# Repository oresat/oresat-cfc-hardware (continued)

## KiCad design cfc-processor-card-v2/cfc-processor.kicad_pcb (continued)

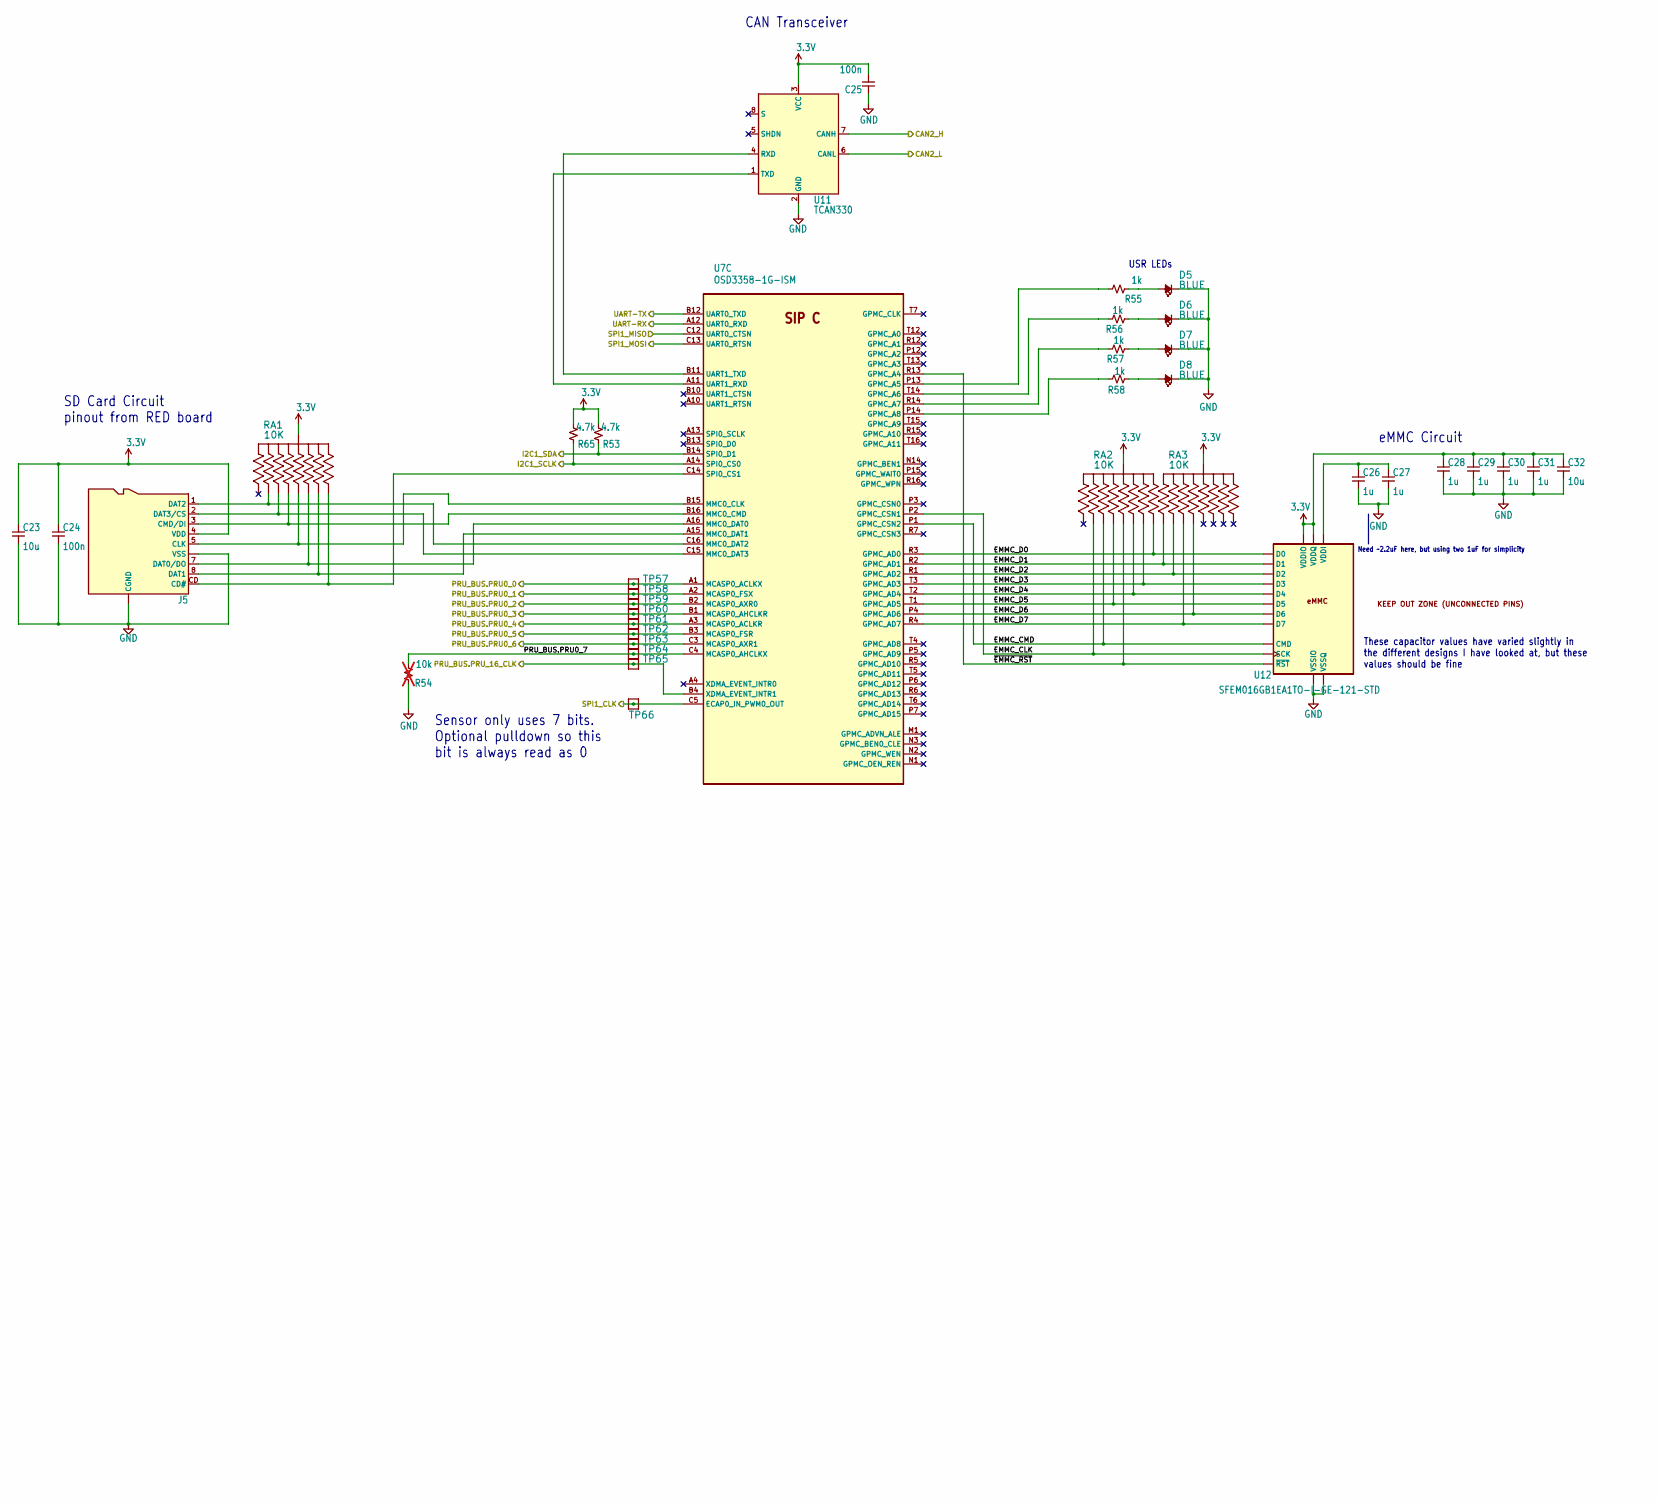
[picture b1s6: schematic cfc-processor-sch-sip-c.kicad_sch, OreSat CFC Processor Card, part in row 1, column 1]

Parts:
C23, C32: 10u; 0805-C-NOSILK; MPN GRT21BC71E106KE13K
C24, C25: 100n; 0603-C-NOSILK; MPN C0603C104K5RACAUTO
C26, C27, C28, C29, C30, C31: 1u; 0603-C-NOSILK; MPN GCM21BR71H105KA03L
D5, D6, D7, D8: BLUE; LED_0603_1608Metric; MPN 150060BS75000
J5: DM3BT-DSF-PEJS; J-Hirose-DM3BT-DSF-PEJS; MPN DM3BT-DSF-PEJS
R53, R65: 4.7k; 0603-C-NOSILK; MPN RMCF0603FT4K70
R54: 10k; 0603-C-NOSILK; not fitted
R55, R56, R57, R58: 1k; 0603-C-NOSILK; MPN RMCF0603FT1K00
RA1, RA2, RA3: 10K; ARRAY_EXBA-M; MPN EXB-A10P103J
TP57, TP58, TP59, TP60, TP61, TP62, TP63, TP64, TP65, TP66: TEST-POINT; 2MM-TEST-POINT
U7: OSD3358-1G-ISM; U-Octavo-OSD335X-BGA-256; MPN OSD3358-1G-ISM
U11: TCAN330; SOT-23-8; MPN TCAN330GDCNT
U12: SFEM016GB1EA1TO-I-GE-121-STD; BGA-153(11.5X13)(EMMC-BA); MPN SFEM016GB1EA1TO-I-GE-121-STD

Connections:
3.3V: C23.1, C24.1, C25.2, C28.1, C29.1, C30.1, C31.1, C32.1, J5.4 (VDD), R53.2, R65.2, RA1.5 (55), RA1.10 (55), RA2.5 (55), RA2.10 (55), RA3.5 (55), RA3.10 (55), U11.3 (VCC), U12.C6 (VDDQ), U12.E6 (VDDIO), U12.F5 (VDDIO), U12.J10 (VDDIO), U12.K9 (VDDIO), U12.M4 (VDDQ), U12.N4 (VDDQ), U12.P3 (VDDQ), U12.P5 (VDDQ); also elsewhere on the board
/CAN2_H: U11.7 (CANH); also elsewhere on the board
/CAN2_L: U11.6 (CANL); also elsewhere on the board
/Deserializer/PRU_BUS.PRU0_0: TP57.1 (1_1), U7.A1 (MCASP0_ACLKX); also elsewhere on the board
/Deserializer/PRU_BUS.PRU0_1: TP58.1 (1_1), U7.A2 (MCASP0_FSX); also elsewhere on the board
/Deserializer/PRU_BUS.PRU0_2: TP59.1 (1_1), U7.B2 (MCASP0_AXR0); also elsewhere on the board
/Deserializer/PRU_BUS.PRU0_3: TP60.1 (1_1), U7.B1 (MCASP0_AHCLKR); also elsewhere on the board
/Deserializer/PRU_BUS.PRU0_4: TP61.1 (1_1), U7.A3 (MCASP0_ACLKR); also elsewhere on the board
/Deserializer/PRU_BUS.PRU0_5: TP62.1 (1_1), U7.B3 (MCASP0_FSR); also elsewhere on the board
/Deserializer/PRU_BUS.PRU0_6: TP63.1 (1_1), U7.C3 (MCASP0_AXR1); also elsewhere on the board
/Deserializer/PRU_BUS.PRU_16_CLK: TP65.1 (1_1), U7.B4 (XDMA_EVENT_INTR1); also elsewhere on the board
/I2C1_CLK: R65.1, U7.A14 (SPI0_CS0); also elsewhere on the board
/I2C1_SDA: R53.1, U7.B14 (SPI0_D1); also elsewhere on the board
/OSD3358: SIP C/EMMC_CLK: RA2.9 (99), U7.P2 (GPMC_CSN1), U12.M6 (SCK)
/OSD3358: SIP C/EMMC_CMD: RA2.2 (22), U7.P1 (GPMC_CSN2), U12.M5 (CMD)
/OSD3358: SIP C/EMMC_D0: RA2.6 (66), U7.R3 (GPMC_AD0), U12.A3 (D0)
/OSD3358: SIP C/EMMC_D1: RA3.1 (11), U7.R2 (GPMC_AD1), U12.A4 (D1)
/OSD3358: SIP C/EMMC_D2: RA3.9 (99), U7.R1 (GPMC_AD2), U12.A5 (D2)
/OSD3358: SIP C/EMMC_D3: RA2.4 (44), U7.T3 (GPMC_AD3), U12.B2 (D3)
/OSD3358: SIP C/EMMC_D4: RA2.7 (77), U7.T2 (GPMC_AD4), U12.B3 (D4)
/OSD3358: SIP C/EMMC_D5: RA2.8 (88), U7.T1 (GPMC_AD5), U12.B4 (D5)
/OSD3358: SIP C/EMMC_D6: RA3.8 (88), U7.P4 (GPMC_AD6), U12.B5 (D6)
/OSD3358: SIP C/EMMC_D7: RA3.2 (22), U7.R4 (GPMC_AD7), U12.B6 (D7)
/OSD3358: SIP C/PRU_BUS.PRU0_7: R54.2, TP64.1 (1_1), U7.C4 (MCASP0_AHCLKX)
/OSD3358: SIP C/UART-RX: U7.A12 (UART0_RXD); also elsewhere on the board
/OSD3358: SIP C/UART-TX: U7.B12 (UART0_TXD); also elsewhere on the board
/OSD3358: SIP C/~EMMC_RST: RA2.3 (33), U7.R13 (GPMC_A4), U12.K5 (~RST)
/SPI1_CLK: TP66.1 (1_1), U7.C5 (ECAP0_IN_PWM0_OUT); also elsewhere on the board
/SPI1_MISO: U7.C12 (UART0_CTSN); also elsewhere on the board
/SPI1_MOSI: U7.C13 (UART0_RTSN); also elsewhere on the board
GND: C23.2, C24.2, C25.1, C26.2, C27.2, C28.2, C29.2, C30.2, C31.2, C32.2, D5.1 (K), D6.1 (K), D7.1 (K), D8.1 (K), J5.6 (VSS), J5.CGND1 (CGND), J5.CGND2 (CGND), J5.CGND3 (CGND), J5.CGND4 (CGND), J5.CGND5 (CGND), J5.CGND6 (CGND), J5.GND (VSS), R54.1, U11.2 (GND), U12.A6 (VSSIO), U12.C4 (VSSQ), U12.E7 (VSSIO), U12.G5 (VSSIO), U12.H10 (VSSIO), U12.J5 (VSSIO), U12.K8 (VSSIO), U12.N2 (VSSQ), U12.N5 (VSSQ), U12.P4 (VSSQ), U12.P6 (VSSQ); also elsewhere on the board
unnamed: D5.2 (A), R55.2
unnamed: D6.2 (A), R56.2
unnamed: D7.2 (A), R57.2
unnamed: D8.2 (A), R58.2
unnamed: J5.CD (CD#), RA1.6 (66), U7.C14 (SPI0_CS1)
unnamed: J5.5 (CLK), RA1.3 (33), U7.B15 (MMC0_CLK)
unnamed: J5.3 (CMD/DI), RA1.8 (88), U7.B16 (MMC0_CMD)
unnamed: J5.7 (DAT0/DO), RA1.7 (77), U7.A16 (MMC0_DAT0)
unnamed: J5.8 (DAT1), RA1.4 (44), U7.A15 (MMC0_DAT1)
unnamed: J5.1 (DAT2), RA1.9 (99), U7.C16 (MMC0_DAT2)
unnamed: J5.2 (DAT3/CS), RA1.2 (22), U7.C15 (MMC0_DAT3)
unnamed: R55.1, U7.P13 (GPMC_A5)
unnamed: R56.1, U7.T14 (GPMC_A6)
unnamed: R57.1, U7.R14 (GPMC_A7)
unnamed: R58.1, U7.P14 (GPMC_A8)
unnamed: U7.B11 (UART1_TXD), U11.4 (RXD)
unnamed: U7.A11 (UART1_RXD), U11.1 (TXD)
unnamed: C26.1, C27.1, U12.C2 (VDDI)

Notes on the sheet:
USR LEDs
Sensor only uses 7 bits. Optional pulldown so this bit is always read as 0
Need ~2.2uF here, but using two 1uF for simplicity
SD Card Circuit pinout from RED board
1.2
These capacitor values have varied slightly in the different designs I have looked at, but these values should be fine
CAN Transceiver
eMMC Circuit

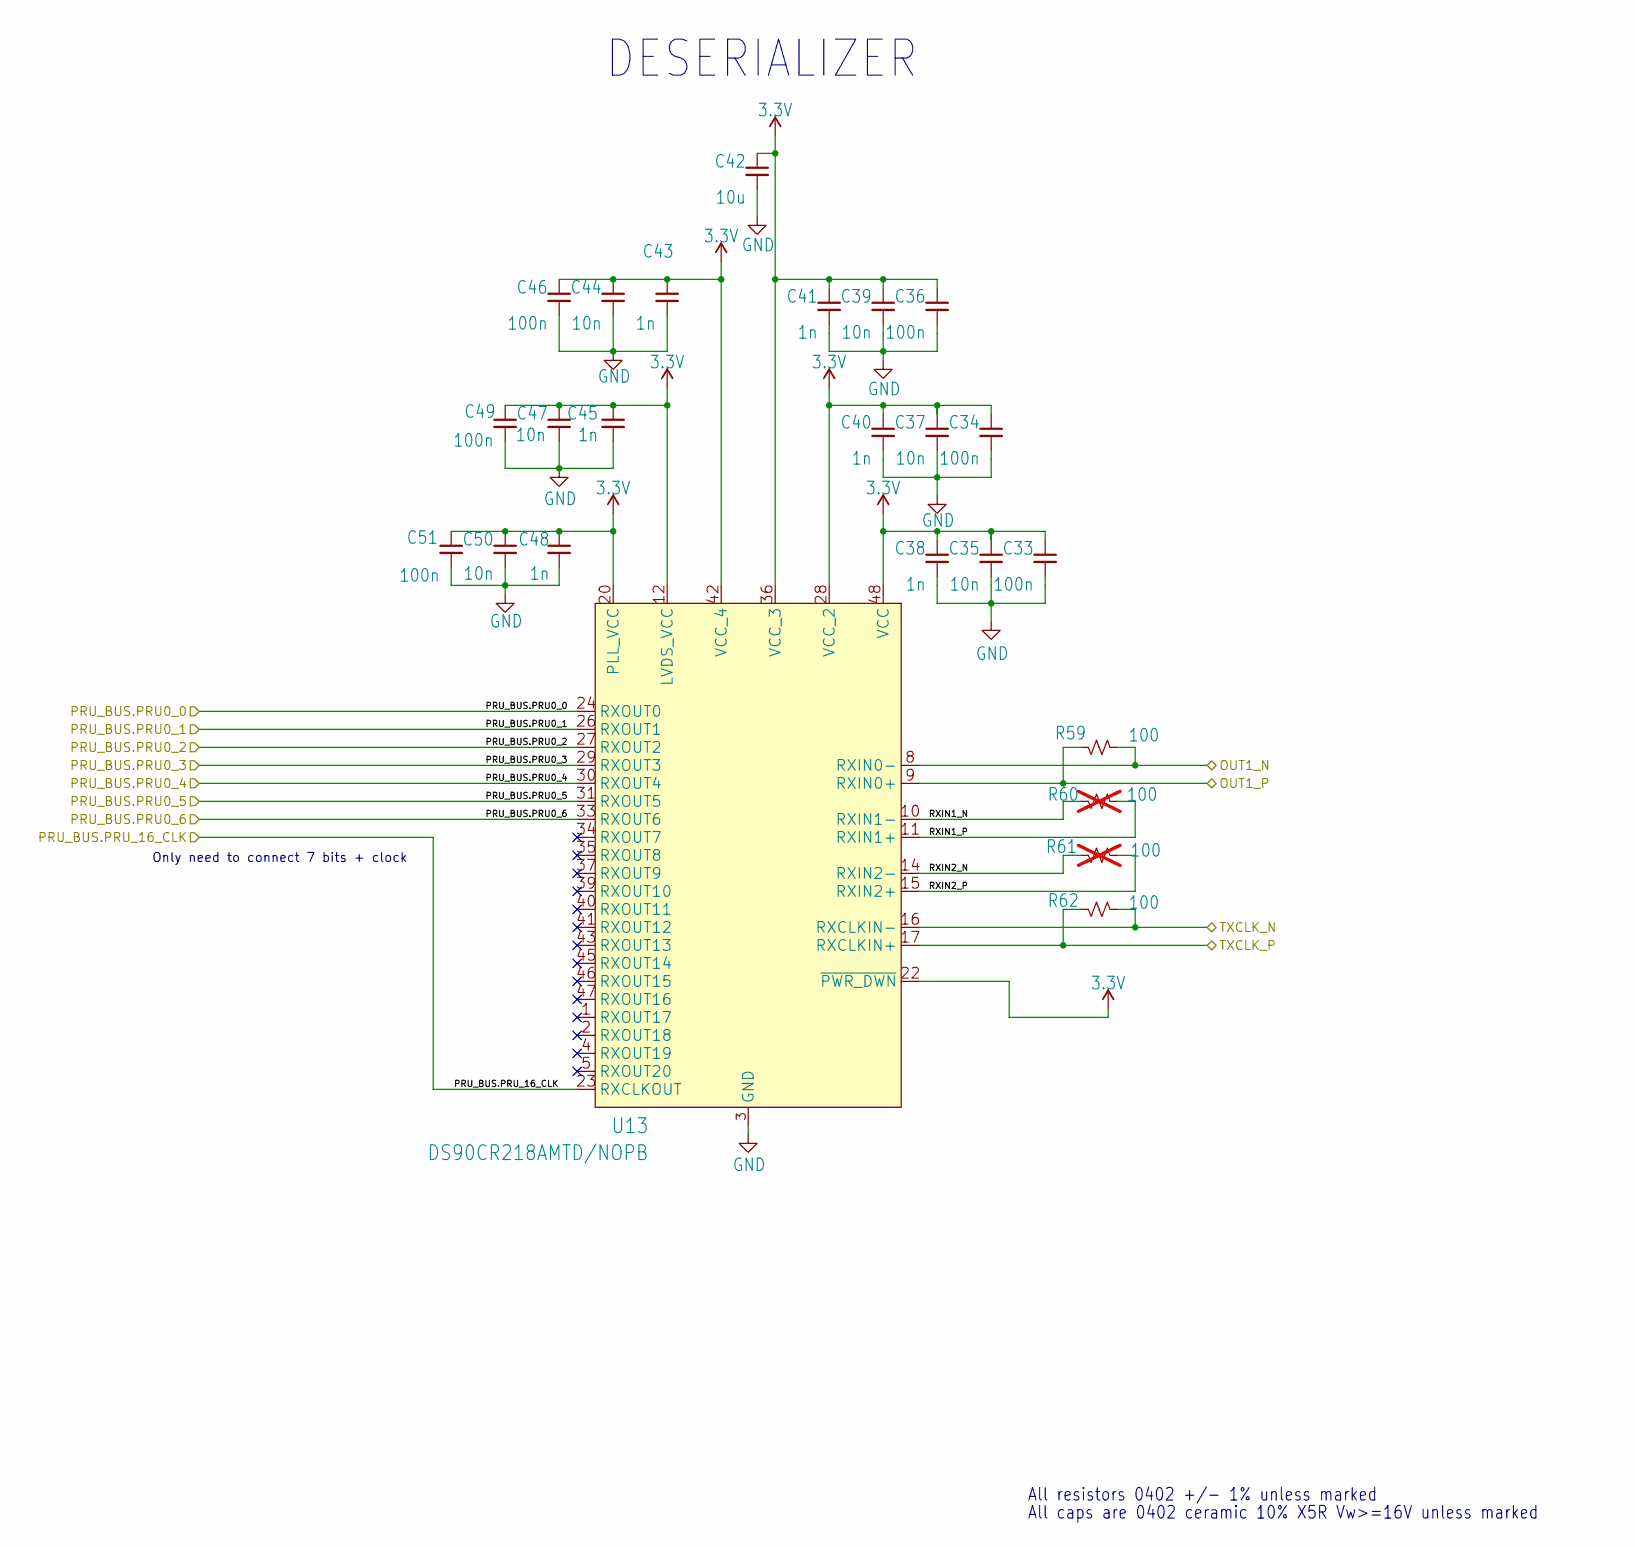
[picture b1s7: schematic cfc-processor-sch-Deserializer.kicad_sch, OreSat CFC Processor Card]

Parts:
C33, C34, C36, C46, C49, C51: 100n; 0402-C-NOSILK; MPN C0402C104K4RECAUTO
C35, C37, C39, C44, C47, C50: 10n; 0402-C-NOSILK; MPN GXT155R71E103KE01D
C38, C40, C41, C43, C45, C48: 1n; 0402-C-NOSILK; MPN C0402C102J3GACAUTO
C42: 10u; 0805-C-NOSILK; MPN GRT21BC71E106KE13K
R59, R62: 100; 0402-C-NOSILK; MPN RMCF0402FT100R
R60, R61: 100; 0402-C-NOSILK; MPN RC0201FR-07100RL; not fitted
U13: DS90CR218AMTD/NOPB; MTD48_TEX-L; MPN DS90CR218AMTD/NOPB

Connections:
3.3V: C33.1, C34.1, C35.1, C36.1, C37.1, C38.1, C39.1, C40.1, C41.1, C42.1, C43.1, C44.1, C45.1, C46.1, C47.1, C48.1, C49.1, C50.1, C51.1, U13.12 (LVDS_VCC), U13.20 (PLL_VCC), U13.22 (~PWR_DWN), U13.28 (VCC_2), U13.36 (VCC_3), U13.42 (VCC_4), U13.48 (VCC); also elsewhere on the board
/Deserializer/PRU_BUS.PRU0_0: U13.24 (RXOUT0); also elsewhere on the board
/Deserializer/PRU_BUS.PRU0_1: U13.26 (RXOUT1); also elsewhere on the board
/Deserializer/PRU_BUS.PRU0_2: U13.27 (RXOUT2); also elsewhere on the board
/Deserializer/PRU_BUS.PRU0_3: U13.29 (RXOUT3); also elsewhere on the board
/Deserializer/PRU_BUS.PRU0_4: U13.30 (RXOUT4); also elsewhere on the board
/Deserializer/PRU_BUS.PRU0_5: U13.31 (RXOUT5); also elsewhere on the board
/Deserializer/PRU_BUS.PRU0_6: U13.33 (RXOUT6); also elsewhere on the board
/Deserializer/PRU_BUS.PRU_16_CLK: U13.23 (RXCLKOUT); also elsewhere on the board
/Deserializer/RXIN1_N: R60.2, U13.10 (RXIN1-)
/Deserializer/RXIN1_P: R60.1, U13.11 (RXIN1+)
/Deserializer/RXIN2_N: R61.2, U13.14 (RXIN2-)
/Deserializer/RXIN2_P: R61.1, U13.15 (RXIN2+)
/OUT1_N: R59.2, U13.8 (RXIN0-); also elsewhere on the board
/OUT1_P: R59.1, U13.9 (RXIN0+); also elsewhere on the board
/TXCLK_N: R62.1, U13.16 (RXCLKIN-); also elsewhere on the board
/TXCLK_P: R62.2, U13.17 (RXCLKIN+); also elsewhere on the board
GND: C33.2, C34.2, C35.2, C36.2, C37.2, C38.2, C39.2, C40.2, C41.2, C42.2, C43.2, C44.2, C45.2, C46.2, C47.2, C48.2, C49.2, C50.2, C51.2, U13.3 (GND), U13.7 (GND), U13.13 (GND), U13.18 (GND), U13.19 (GND), U13.21 (GND), U13.25 (GND), U13.32 (GND), U13.38 (GND), U13.44 (GND); also elsewhere on the board

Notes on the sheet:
All caps are 0402 ceramic 10% X5R Vw>=16V unless marked
All resistors 0402 +/- 1% unless marked
Only need to connect 7 bits + clock
DESERIALIZER

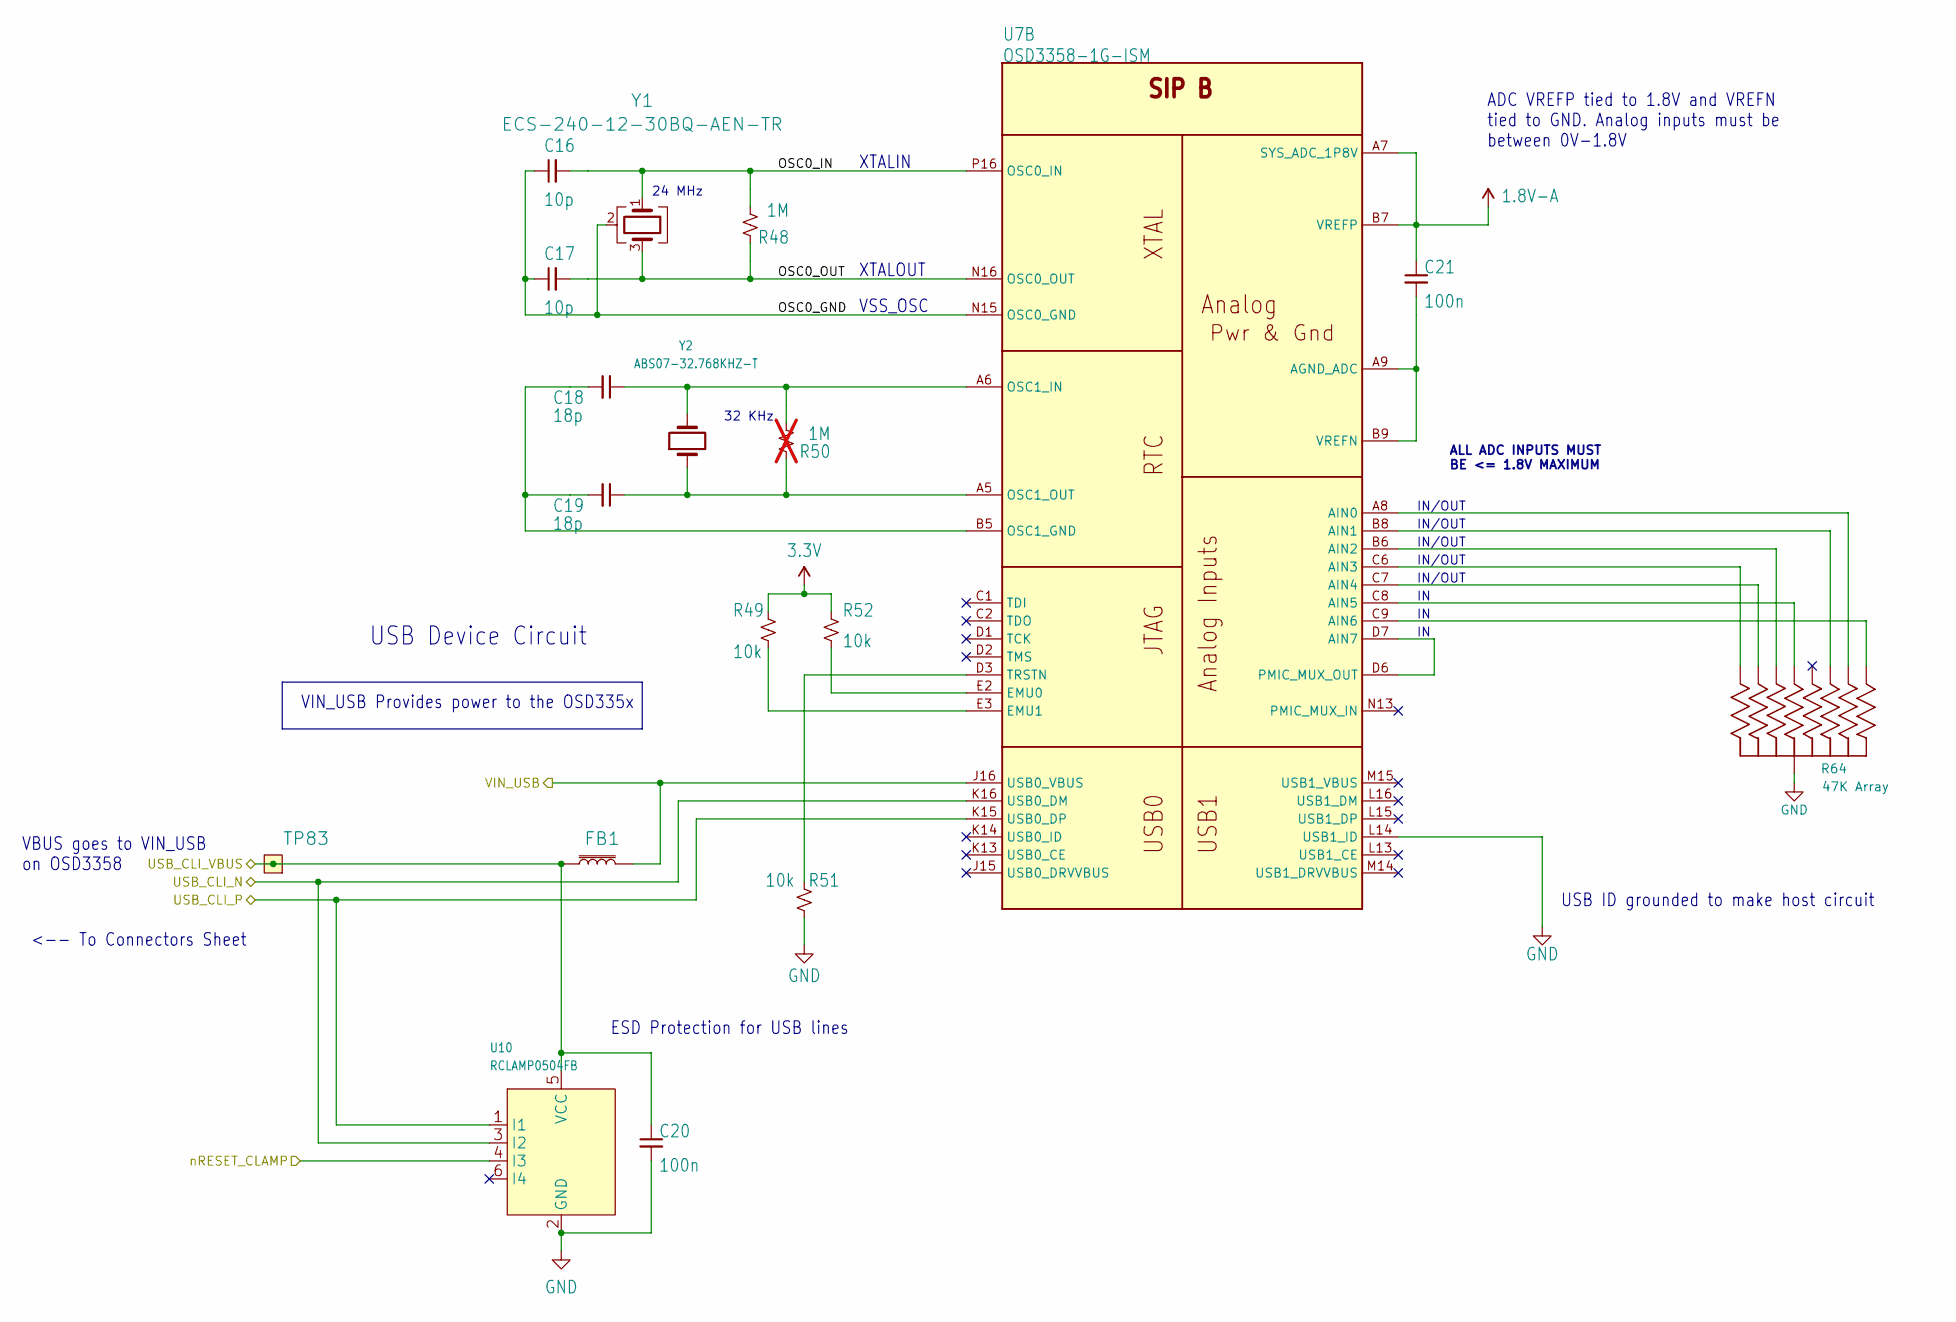
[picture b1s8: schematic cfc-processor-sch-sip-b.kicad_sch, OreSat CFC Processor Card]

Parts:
C16, C17: 10p; 0603-C-NOSILK; MPN C0603C100J1GACAUTO
C18, C19: 18p; 0603-C-NOSILK; MPN C0603C180J1GACAUTO
C20, C21: 100n; 0603-C-NOSILK; MPN C0603C104K5RACAUTO
FB1: BLM18KG300JH1D; L_0603_1608Metric; MPN BLM18KG300JH1D
R48: 1M; 0603-C-NOSILK; MPN RMCF0603FG1M00
R49, R51, R52: 10k; 0603-C-NOSILK; MPN RMCF0603FT10K0
R50: 1M; 0603-C-NOSILK; not fitted
R64: 47K Array; ARRAY_EXBA-M; MPN EXB-A10P473J
TP83: TEST-POINT; TestPoint-0.75mm-th
U7: OSD3358-1G-ISM; U-Octavo-OSD335X-BGA-256; MPN OSD3358-1G-ISM
U10: RCLAMP0504FB; SC70-6; MPN RCLAMP0504FBTCT
Y1: ECS-240-12-30BQ-AEN-TR; CRYSTAL-5X3.2-4SMD; MPN ECS-240-12-30BQ-AEN-TR
Y2: ABS07-32.768KHZ-T; CRYSTAL_3.2X1.5; MPN ABS07-32.768KHZ-T

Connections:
1.8V-A: C21.1, U7.A7 (SYS_ADC_1P8V), U7.B7 (VREFP)
3.3V: R49.2, R52.2; also elsewhere on the board
/OSD3358: SIP A (PWR)/NRESET: U10.4 (I3); also elsewhere on the board
/OSD3358: SIP A (PWR)/VIN_USB: FB1.2, U7.J16 (USB0_VBUS); also elsewhere on the board
/OSD3358: SIP B/OSC0_GND: C16.1, C17.1, U7.N15 (OSC0_GND), Y1.2 (G), Y1.4 (G)
/OSD3358: SIP B/OSC0_IN: C16.2, R48.2, U7.P16 (OSC0_IN), Y1.1
/OSD3358: SIP B/OSC0_OUT: C17.2, R48.1, U7.N16 (OSC0_OUT), Y1.3
/OSD3358: SIP B/USB_CLI_N: U7.K16 (USB0_DM), U10.3 (I2); also elsewhere on the board
/OSD3358: SIP B/USB_CLI_P: U7.K15 (USB0_DP), U10.1 (I1); also elsewhere on the board
/OSD3358: SIP B/USB_CLI_VBUS: C20.1, FB1.1, TP83.1 (1_1), U10.5 (VCC); also elsewhere on the board
GND: C20.2, R51.1, R64.5 (55), R64.10 (55), U7.L14 (USB1_ID), U10.2 (GND); also elsewhere on the board
unnamed: R64.1 (11), U7.C9 (AIN6)
unnamed: R64.2 (22), U7.B8 (AIN1)
unnamed: R64.3 (33), U7.C8 (AIN5)
unnamed: R64.4 (44), U7.C7 (AIN4)
unnamed: R64.6 (66), U7.C6 (AIN3)
unnamed: R64.7 (77), U7.B6 (AIN2)
unnamed: R64.9 (99), U7.A8 (AIN0)
unnamed: C21.2, U7.A9 (AGND_ADC), U7.B9 (VREFN)
unnamed: U7.D6 (PMIC_MUX_OUT), U7.D7 (AIN7)
unnamed: R52.1, U7.E2 (EMU0)
unnamed: R49.1, U7.E3 (EMU1)
unnamed: C18.2, C19.2, U7.B5 (OSC1_GND)
unnamed: C18.1, R50.2, U7.A6 (OSC1_IN), Y2.2
unnamed: C19.1, R50.1, U7.A5 (OSC1_OUT), Y2.1
unnamed: R51.2, U7.D3 (TRSTN)

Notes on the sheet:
XTALOUT
IN/OUT
<-- To Connectors Sheet
USB ID grounded to make host circuit
VSS_OSC
ADC VREFP tied to 1.8V and VREFN tied to GND. Analog inputs must be between 0V-1.8V
VBUS goes to VIN_USB on OSD3358
USB Device Circuit
VIN_USB Provides power to the OSD335x
ESD Protection for USB lines
24 MHz
ALL ADC INPUTS MUST BE <= 1.8V MAXIMUM
32 KHz
XTALIN

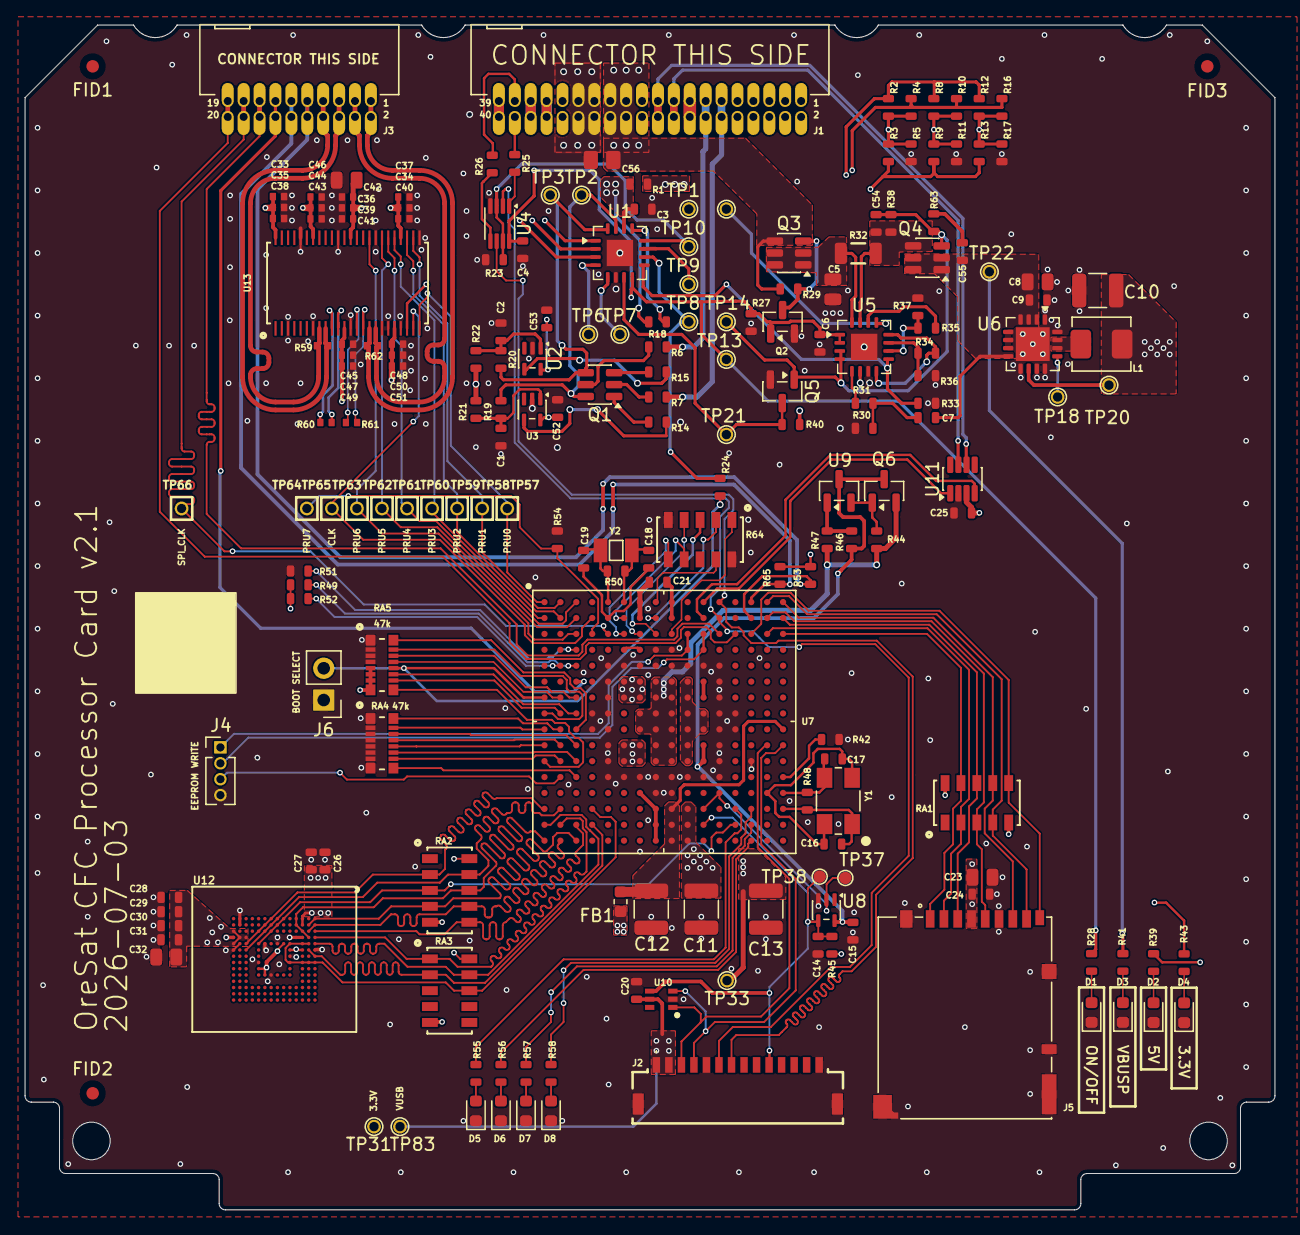
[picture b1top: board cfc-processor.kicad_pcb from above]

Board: 4 copper layers, 99.8 x 94.6 mm, 196 parts (0 on the bottom side), 165 nets.

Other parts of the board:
PCB1: ORESAT-CARD-V1.3-GENERIC-0RF

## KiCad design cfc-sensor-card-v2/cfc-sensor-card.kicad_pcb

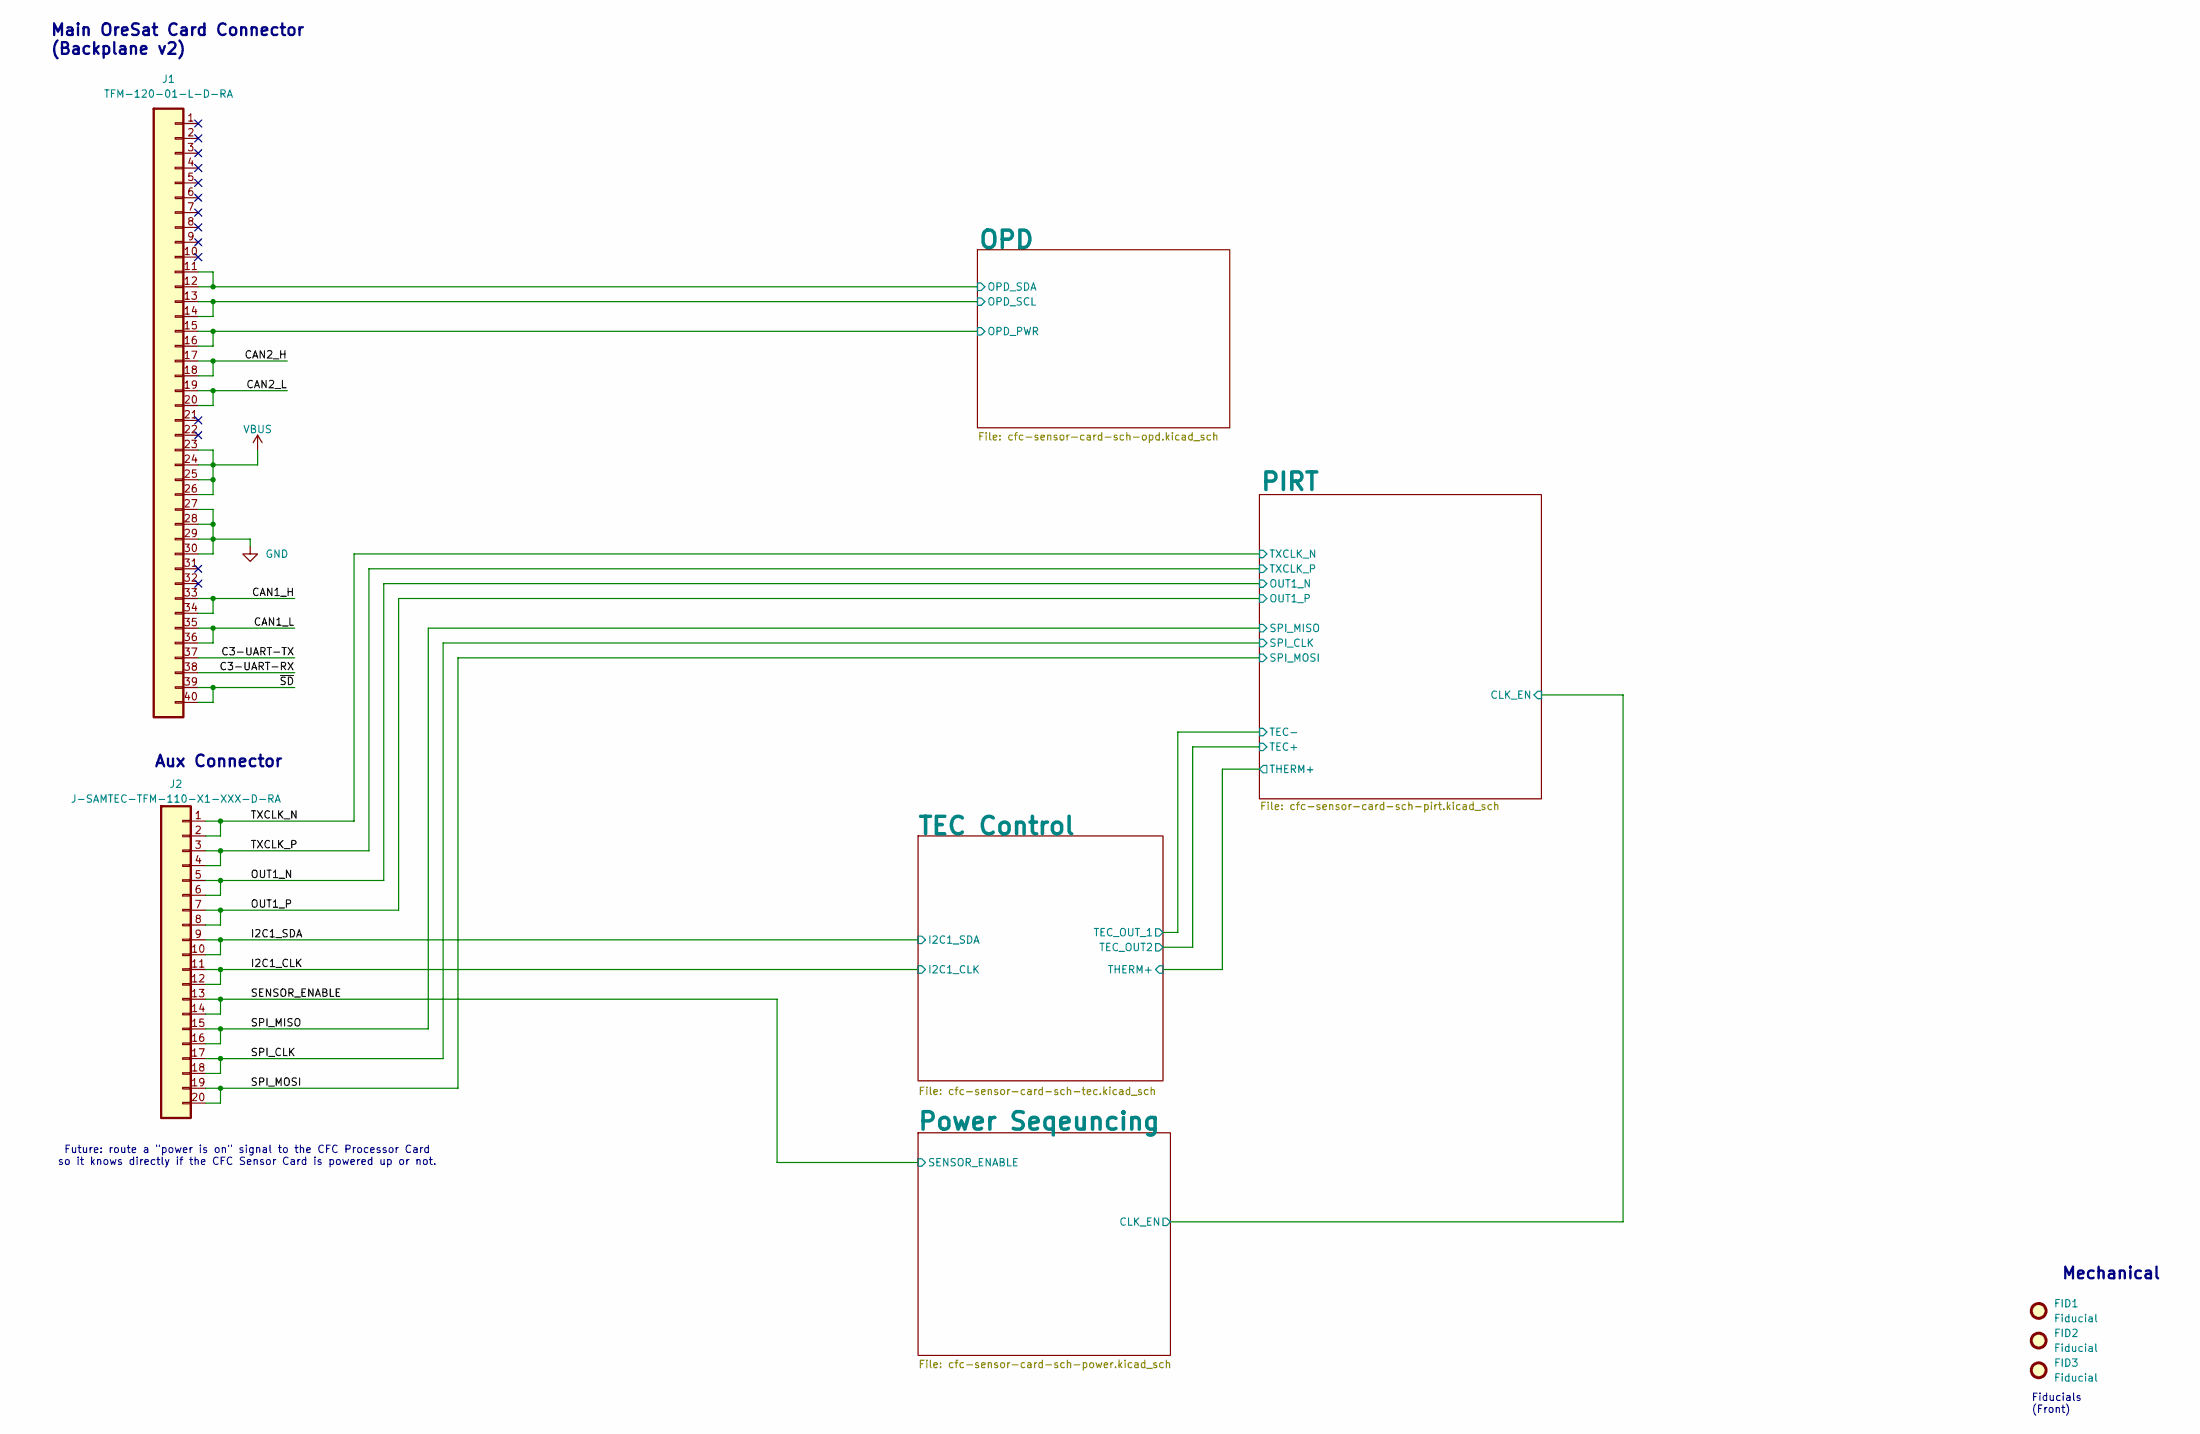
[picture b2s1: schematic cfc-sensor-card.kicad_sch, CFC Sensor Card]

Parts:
FID1, FID2, FID3: Fiducial; Fiducial_1mm_Mask2mm
J1: TFM-120-01-L-D-RA; J-SAMTEC-TFM-120-X1-XXX-D-RA; MPN TFM-120-01-L-D-RA
J2: J-SAMTEC-TFM-110-X1-XXX-D-RA; MPN TFM-110-01-L-D-RA

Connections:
/C3-UART-RX: J1.38
/C3-UART-TX: J1.37
/CAN1_H: J1.33, J1.34
/CAN1_L: J1.35, J1.36
/CAN2_H: J1.17, J1.18
/CAN2_L: J1.19, J1.20
/I2C1_CLK: J2.11, J2.12; also elsewhere on the board
/I2C1_SDA: J2.9, J2.10; also elsewhere on the board
/OPD/OPD_PWR: J1.15, J1.16; also elsewhere on the board
/OPD/OPD_SCL: J1.13, J1.14; also elsewhere on the board
/OPD/OPD_SDA: J1.11, J1.12; also elsewhere on the board
/OUT1_N: J2.5, J2.6; also elsewhere on the board
/OUT1_P: J2.7, J2.8; also elsewhere on the board
/SENSOR_ENABLE: J2.13, J2.14; also elsewhere on the board
/SPI_CLK: J2.17, J2.18; also elsewhere on the board
/SPI_MISO: J2.15, J2.16; also elsewhere on the board
/SPI_MOSI: J2.19, J2.20; also elsewhere on the board
/TXCLK_N: J2.1, J2.2; also elsewhere on the board
/TXCLK_P: J2.3, J2.4; also elsewhere on the board
/~SD: J1.39, J1.40
VBUS: J1.23, J1.24, J1.25, J1.26; also elsewhere on the board

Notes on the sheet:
Mechanical
Aux Connector
Fiducials (Front)
Future: route a "power is on" signal to the CFC Processor Card so it knows directly if the CFC Sensor Card is powered up or not.
Main OreSat Card Connector (Backplane v2)
